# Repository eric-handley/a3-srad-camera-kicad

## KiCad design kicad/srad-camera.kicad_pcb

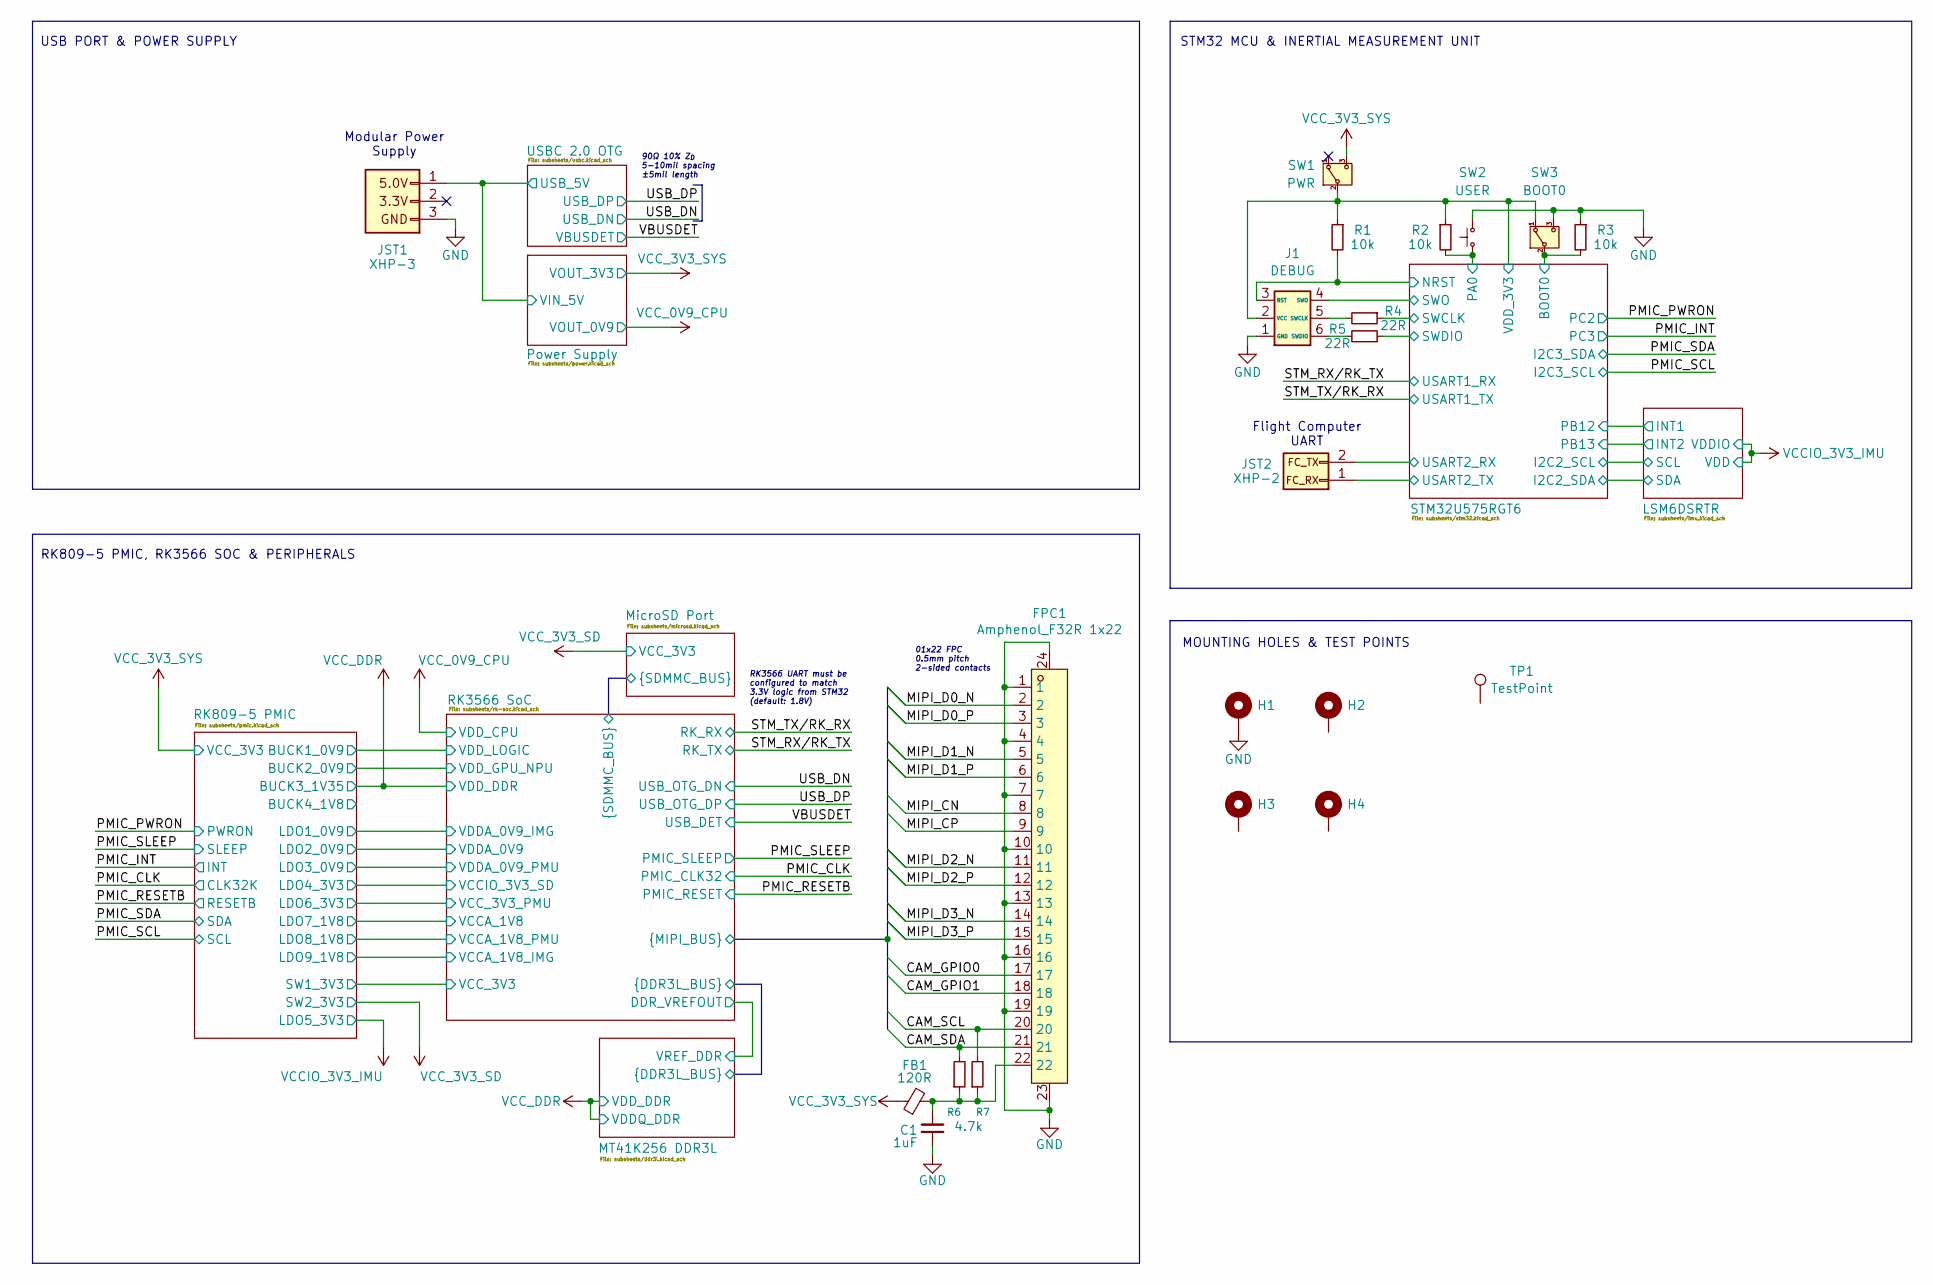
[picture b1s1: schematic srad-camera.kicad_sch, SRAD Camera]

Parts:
C1: 1uF; C_0603_1608Metric; LCSC PART NAME C15849
FB1: 120R; R_0201_0603Metric; LCSC PART NAME C14709
FPC1: Amphenol_F32R 1x22; AMPHENOL_10051922-2210ELF; MANUFACTURER PART 0.5K-AX-22PWB; JLCPCB PART CLASS Extended Part
H1, H2, H3, H4: MntHole; 4-40_MountingHole
J1: DEBUG; PinHeader_2x03_P1.27mm_Vertical
JST1: XHP-3; JST_XH_B3B-XH-A_1x03_P2.50mm_Vertical
JST2: XHP-2; JST_XH_B2B-XH-A_1x02_P2.50mm_Vertical
R1, R2, R3: 10k; R_0402_1005Metric; LCSC PART NAME C25744
R4, R5: 22R; R_0402_1005Metric; LCSC PART NAME C25092
R6, R7: 4.7k; R_0402_1005Metric; LCSC PART NAME C25900
SW1: PWR; SW_SPDT_PCM12
SW2: USER; SW_SPST_EVQP2_MiddlePushTravel_H2.5mm
SW3: BOOT0; SW_SPDT_PCM12
TP1: TestPoint

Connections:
/Power Supply/VIN_5V: JST1.1; also elsewhere on the board
/RK3566 SoC/CAM_GPIO0: FPC1.17; also elsewhere on the board
/RK3566 SoC/CAM_GPIO1: FPC1.18; also elsewhere on the board
/RK3566 SoC/CAM_SCL: FPC1.20, R7.2; also elsewhere on the board
/RK3566 SoC/CAM_SDA: FPC1.21, R6.2; also elsewhere on the board
/RK3566 SoC/MIPI_CN: FPC1.8; also elsewhere on the board
/RK3566 SoC/MIPI_CP: FPC1.9; also elsewhere on the board
/RK3566 SoC/MIPI_D0_N: FPC1.2; also elsewhere on the board
/RK3566 SoC/MIPI_D0_P: FPC1.3; also elsewhere on the board
/RK3566 SoC/MIPI_D1_N: FPC1.5; also elsewhere on the board
/RK3566 SoC/MIPI_D1_P: FPC1.6; also elsewhere on the board
/RK3566 SoC/MIPI_D2_N: FPC1.11; also elsewhere on the board
/RK3566 SoC/MIPI_D2_P: FPC1.12; also elsewhere on the board
/RK3566 SoC/MIPI_D3_N: FPC1.14; also elsewhere on the board
/RK3566 SoC/MIPI_D3_P: FPC1.15; also elsewhere on the board
/STM32U575RGT6/BOOT0: R3.2, SW3.2 (B); also elsewhere on the board
/STM32U575RGT6/NRST: J1.3 (RST), R1.2; also elsewhere on the board
/STM32U575RGT6/PA0: R2.2, SW2.1; also elsewhere on the board
/STM32U575RGT6/SWCLK: R4.1; also elsewhere on the board
/STM32U575RGT6/SWDIO: R5.1; also elsewhere on the board
/STM32U575RGT6/SWO: J1.4 (SWO); also elsewhere on the board
/STM32U575RGT6/USART2_RX: JST2.2; also elsewhere on the board
/STM32U575RGT6/USART2_TX: JST2.1; also elsewhere on the board
/STM32U575RGT6/VDD_3V3: J1.2 (VCC), R1.1, R2.1, SW1.2 (B), SW3.1 (A); also elsewhere on the board
GND: C1.1, FPC1.1, FPC1.4, FPC1.7, FPC1.10, FPC1.13, FPC1.16, FPC1.19, FPC1.23, FPC1.24, H1.1 (MP), J1.1 (GND), JST1.3, R3.1, SW2.2, SW3.3 (C); also elsewhere on the board
unnamed: C1.2, FB1.2, FPC1.22, R6.1, R7.1
unnamed: J1.5 (SWCLK), R4.2
unnamed: J1.6 (SWDIO), R5.2
VCC_3V3_SYS: FB1.1, SW1.3 (C); also elsewhere on the board

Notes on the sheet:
STM32 MCU & INERTIAL MEASUREMENT UNIT
USB PORT & POWER SUPPLY
01x22 FPC 0.5mm pitch 2-sided contacts
90Ω 10% Z_{D} 5-10mil spacing ±5mil length
RK3566 UART must be configured to match 3.3V logic from STM32 (default: 1.8V)
RK809-5 PMIC, RK3566 SOC & PERIPHERALS
Modular Power Supply
Flight Computer UART
MOUNTING HOLES & TEST POINTS

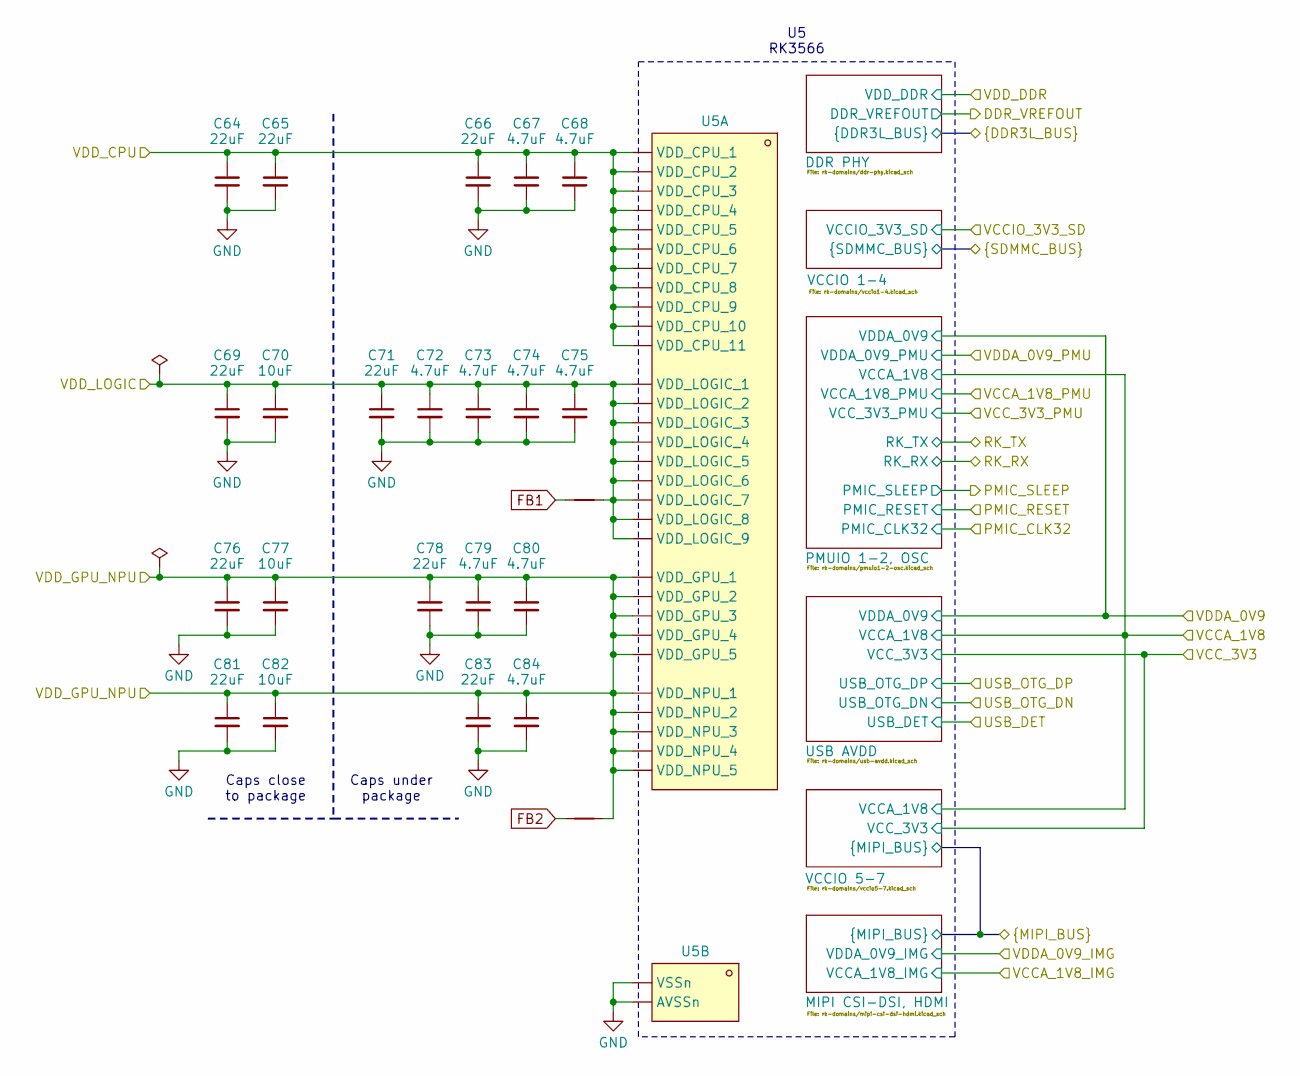
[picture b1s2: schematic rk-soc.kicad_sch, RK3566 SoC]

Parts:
C64, C65, C66, C69, C71, C76, C78, C81, C83: 22uF; C_1206_3216Metric; LCSC PART NAME C12891
C67, C68, C72, C73, C74, C75, C79, C80, C84: 4.7uF; C_0402_1005Metric; LCSC PART NAME C1779
C70, C77, C82: 10uF; C_0805_2012Metric; LCSC PART NAME C15850
NT3, NT4: NetTie_2
U5: RK3566; BGA-565_L15.5-W14.4-P0.40_RK3566_1; MANUFACTURER PART RK3566; JLCPCB PART CLASS Extended Part

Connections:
/RK3566 SoC/VDD_GPU_NPU: C76.1, C77.1, C78.1, C79.1, C80.1, C81.1, C82.1, C83.1, C84.1, NT4.2, U5.1G15 (VDD_NPU_1), U5.1H14 (VDD_NPU_2), U5.1H15 (VDD_NPU_3), U5.1J14 (VDD_NPU_4), U5.1J15 (VDD_NPU_5), U5.1L8 (VDD_GPU_1), U5.1L9 (VDD_GPU_2), U5.1M7 (VDD_GPU_3), U5.1M8 (VDD_GPU_4), U5.1M9 (VDD_GPU_5); also elsewhere on the board
/RK3566 SoC/VDD_LOGIC: C69.1, C70.1, C71.1, C72.1, C73.1, C74.1, C75.1, NT3.2, U5.1H7 (VDD_LOGIC_1), U5.1H8 (VDD_LOGIC_2), U5.1H9 (VDD_LOGIC_3), U5.1H10 (VDD_LOGIC_4), U5.1J7 (VDD_LOGIC_5), U5.1J10 (VDD_LOGIC_6), U5.1K7 (VDD_LOGIC_7), U5.1K10 (VDD_LOGIC_8), U5.1L7 (VDD_LOGIC_9); also elsewhere on the board
GND: C64.2, C65.2, C66.2, C67.2, C68.2, C69.2, C70.2, C71.2, C72.2, C73.2, C74.2, C75.2, C76.2, C77.2, C78.2, C79.2, C80.2, C81.2, C82.2, C83.2, C84.2, U5.1B10 (VSS_30), U5.1B11 (VSS_31), U5.1B15 (VSS_32), U5.1B19 (VSS_33), U5.1C4 (VSS_34), U5.1C5 (VSS_35), U5.1C6 (VSS_36), U5.1C8 (VSS_37), U5.1C9 (VSS_38), U5.1C14 (VSS_39), U5.1C16 (VSS_40), U5.1C18 (VSS_41), U5.1D1 (VSS_42), U5.1D3 (VSS_43), U5.1D10 (VSS_44), U5.1D14 (VSS_45), U5.1E3 (VSS_46), U5.1E8 (VSS_47), U5.1E10 (VSS_48), U5.1E14 (VSS_49), U5.1E15 (VSS_50), U5.1E17 (VSS_51), U5.1F6 (VSS_52), U5.1F7 (VSS_53), U5.1F8 (VSS_54), U5.1F9 (VSS_55), U5.1F10 (VSS_56), U5.1F15 (VSS_57), U5.1F16 (VSS_58), U5.1F20 (AVSS1_6), U5.1G3 (VSS_59), U5.1G6 (VSS_60), U5.1G7 (VSS_61), U5.1G8 (VSS_62), U5.1G9 (VSS_63), U5.1G10 (VSS_64), U5.1G11 (VSS_65), U5.1G12 (VSS_66), U5.1G14 (VSS_67), U5.1G16 (AVSS1_7), U5.1G18 (AVSS1_8), U5.1G19 (AVSS1_9), U5.1G20 (AVSS1_10), U5.1H1 (VSS_68), U5.1H2 (VSS_69), U5.1H6 (VSS_70), U5.1H11 (VSS_71), U5.1H12 (VSS_72), U5.1H13 (VSS_73), U5.1J1 (VSS_74), U5.1J6 (VSS_75), U5.1J8 (VSS_76), U5.1J9 (VSS_77), U5.1J11 (VSS_78), U5.1J12 (VSS_79), U5.1J13 (VSS_80), U5.1J16 (AVSS1_11), U5.1J18 (AVSS1_12), U5.1K2 (VSS_81), U5.1K3 (VSS_82), U5.1K4 (VSS_83), U5.1K5 (VSS_84), U5.1K6 (VSS_85), U5.1K8 (VSS_86), U5.1K9 (VSS_87), U5.1K11 (VSS_88), U5.1K12 (VSS_89), U5.1K13 (VSS_90), U5.1K14 (VSS_91), U5.1K15 (VSS_92), U5.1K18 (AVSS1_13), U5.1L3 (VSS_93), U5.1L6 (VSS_94), U5.1L10 (VSS_95), U5.1L11 (VSS_96), U5.1L12 (VSS_97), U5.1L13 (VSS_98), U5.1L14 (VSS_99), U5.1L15 (VSS_100), U5.1L19 (AVSS1_14), U5.1M3 (VSS_101), U5.1M4 (VSS_102), U5.1M5 (VSS_103), U5.1M6 (VSS_104), U5.1M10 (VSS_105), U5.1M11 (VSS_106), U5.1M12 (VSS_107), U5.1M13 (VSS_108), U5.1M14 (VSS_109), U5.1M15 (VSS_110), U5.1M16 (VSS_111), U5.1M17 (VSS_112), U5.1M20 (VSS_113), U5.1N3 (VSS_114), U5.1N4 (VSS_115), U5.1N7 (VSS_116), U5.1N11 (AVSS_9), U5.1N12 (AVSS_10), U5.1P1 (VSS_117), U5.1P5 (VSS_118), U5.1P6 (VSS_119), U5.1P7 (VSS_120), U5.1P8 (AVSS_11), U5.1P10 (AVSS_12), U5.1P14 (AVSS_13), U5.1P15 (VSS_121), U5.1R3 (VSS_122), U5.1R4 (VSS_123), U5.1R5 (VSS_124), U5.1R6 (VSS_125), U5.1R7 (VSS_126), U5.1R8 (AVSS_14), U5.1R9 (AVSS_15), U5.1R11 (AVSS_16), U5.1R12 (AVSS_17), U5.1R13 (AVSS_18), U5.1R14 (AVSS_19), U5.1R15 (AVSS_20), U5.1T3 (VSS_127), U5.1T5 (VSS_128), U5.1T7 (AVSS_21), U5.1T8 (AVSS_22), U5.1T9 (AVSS_23), U5.1T10 (AVSS_24), U5.1T11 (AVSS_25), U5.1T12 (AVSS_26), U5.1T13 (AVSS_27), U5.1T14 (AVSS_28), U5.1T15 (AVSS_29), U5.1T16 (AVSS_30), U5.1T17 (AVSS_31), U5.1U2 (VSS_129), U5.1U12 (AVSS_32), U5.1U13 (AVSS_33), U5.1U15 (AVSS_34), U5.1U17 (AVSS_35), U5.1V1 (VSS_130), U5.1V4 (VSS_131), U5.1V7 (AVSS_36), U5.1V12 (AVSS_37), U5.1V13 (AVSS_38), U5.1V18 (AVSS_39), U5.A1 (VSSn), U5.A2 (VSS_2), U5.A38 (VSS_3), U5.AA2 (VSS_18), U5.AC37 (VSS_24), U5.AD2 (VSS_19), U5.AE37 (VSS_25), U5.AH37 (VSS_26), U5.AL37 (VSS_27), U5.AP2 (VSS_20), U5.AP8 (VSS_22), U5.AP13 (AVSS_1), U5.AP16 (AVSS_2), U5.AP19 (AVSS_3), U5.AP22 (AVSS_4), U5.AP25 (AVSS_5), U5.AP28 (AVSS_6), U5.AP31 (AVSS_7), U5.AP34 (AVSS_8), U5.AP37 (VSS_28), U5.AR1 (VSS_21), U5.AR38 (VSS_29), U5.B1 (VSS_4), U5.B2 (VSS_5), U5.B6 (VSS_6), U5.B11 (VSS_7), U5.B14 (VSS_8), U5.B18 (VSS_9), U5.B21 (VSS_10), U5.B28 (VSS_11), U5.B31 (VSS_12), U5.D2 (VSS_13), U5.E37 (VSS_23), U5.H37 (AVSSn), U5.J2 (VSS_14), U5.L2 (VSS_15), U5.L37 (AVSS1_2), U5.P37 (AVSS1_3), U5.U2 (VSS_16), U5.U37 (AVSS1_4), U5.W2 (VSS_17), U5.Y37 (AVSS1_5); also elsewhere on the board
VCC_0V9_CPU: C64.1, C65.1, C66.1, C67.1, C68.1, U5.1C12 (VDD_CPU_1), U5.1D11 (VDD_CPU_2), U5.1D12 (VDD_CPU_3), U5.1E11 (VDD_CPU_4), U5.1E12 (VDD_CPU_5), U5.1E13 (VDD_CPU_6), U5.1F11 (VDD_CPU_7), U5.1F12 (VDD_CPU_8), U5.1F13 (VDD_CPU_9), U5.1F14 (VDD_CPU_10), U5.1G13 (VDD_CPU_11); also elsewhere on the board

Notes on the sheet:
U5 RK3566
Caps close to package
Caps under package

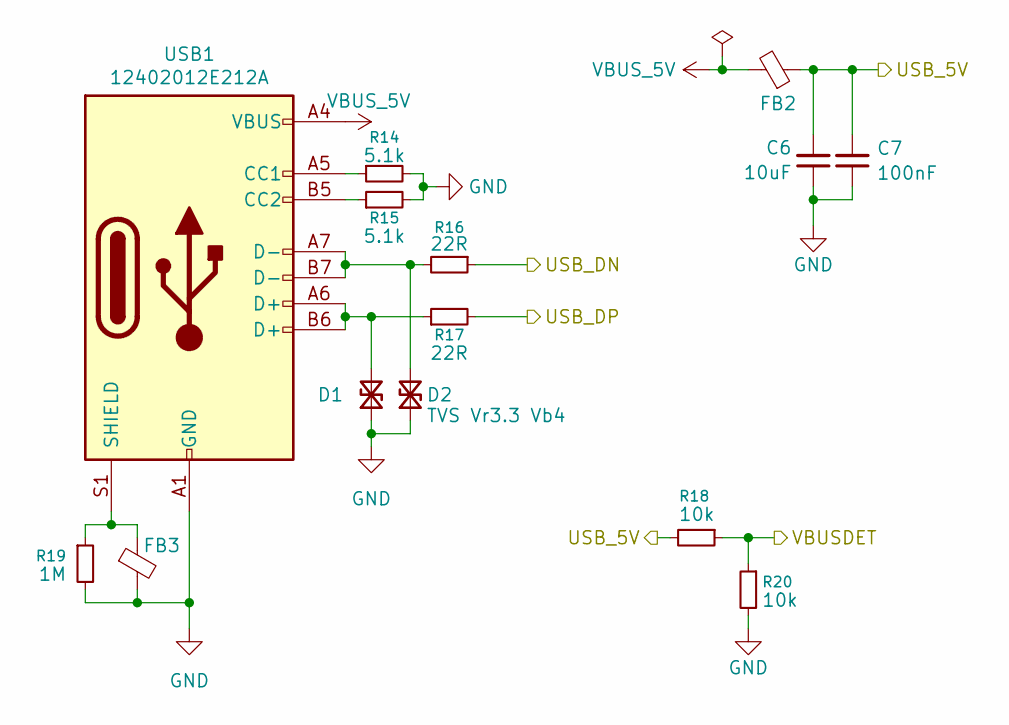
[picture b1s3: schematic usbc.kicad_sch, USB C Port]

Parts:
C6: 10uF; C_0805_2012Metric; LCSC PART NAME C15850
C7: 100nF; C_0402_1005Metric; LCSC PART NAME C1525
D1, D2: TVS Vr3.3 Vb4; D_SOD-123F; LCSC PART NAME C19077496
FB2, FB3: 120R; R_0201_0603Metric; LCSC PART NAME C14709
R14, R15: 5.1k; R_0402_1005Metric; LCSC PART NAME C25905
R16, R17: 22R; R_0402_1005Metric; LCSC PART NAME C25092
R18, R20: 10k; R_0402_1005Metric; LCSC PART NAME C25744
R19: 1M; R_0402_1005Metric; LCSC PART NAME C26083
USB1: 12402012E212A; USB_C_Receptacle_HRO_TYPE-C-31-M-12

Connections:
/Power Supply/VIN_5V: C6.2, C7.2, FB2.1, R18.2; also elsewhere on the board
/USB_DN: R16.1; also elsewhere on the board
/USB_DP: R17.2; also elsewhere on the board
/VBUSDET: R18.1, R20.1; also elsewhere on the board
GND: C6.1, C7.1, D1.1 (A1), D2.1 (A1), FB3.2, R14.2, R15.2, R19.2, R20.2, USB1.A1 (GND), USB1.A12 (GND), USB1.B1 (GND), USB1.B12 (GND); also elsewhere on the board
unnamed: D1.2 (A2), R17.1, USB1.A6 (D+), USB1.B6 (D+)
unnamed: D2.2 (A2), R16.2, USB1.A7 (D-), USB1.B7 (D-)
unnamed: R14.1, USB1.A5 (CC1)
unnamed: R15.1, USB1.B5 (CC2)
unnamed: FB3.1, R19.1, USB1.S1 (SHIELD)
VBUS_5V: FB2.2, USB1.A4 (VBUS), USB1.A9 (VBUS), USB1.B4 (VBUS), USB1.B9 (VBUS)

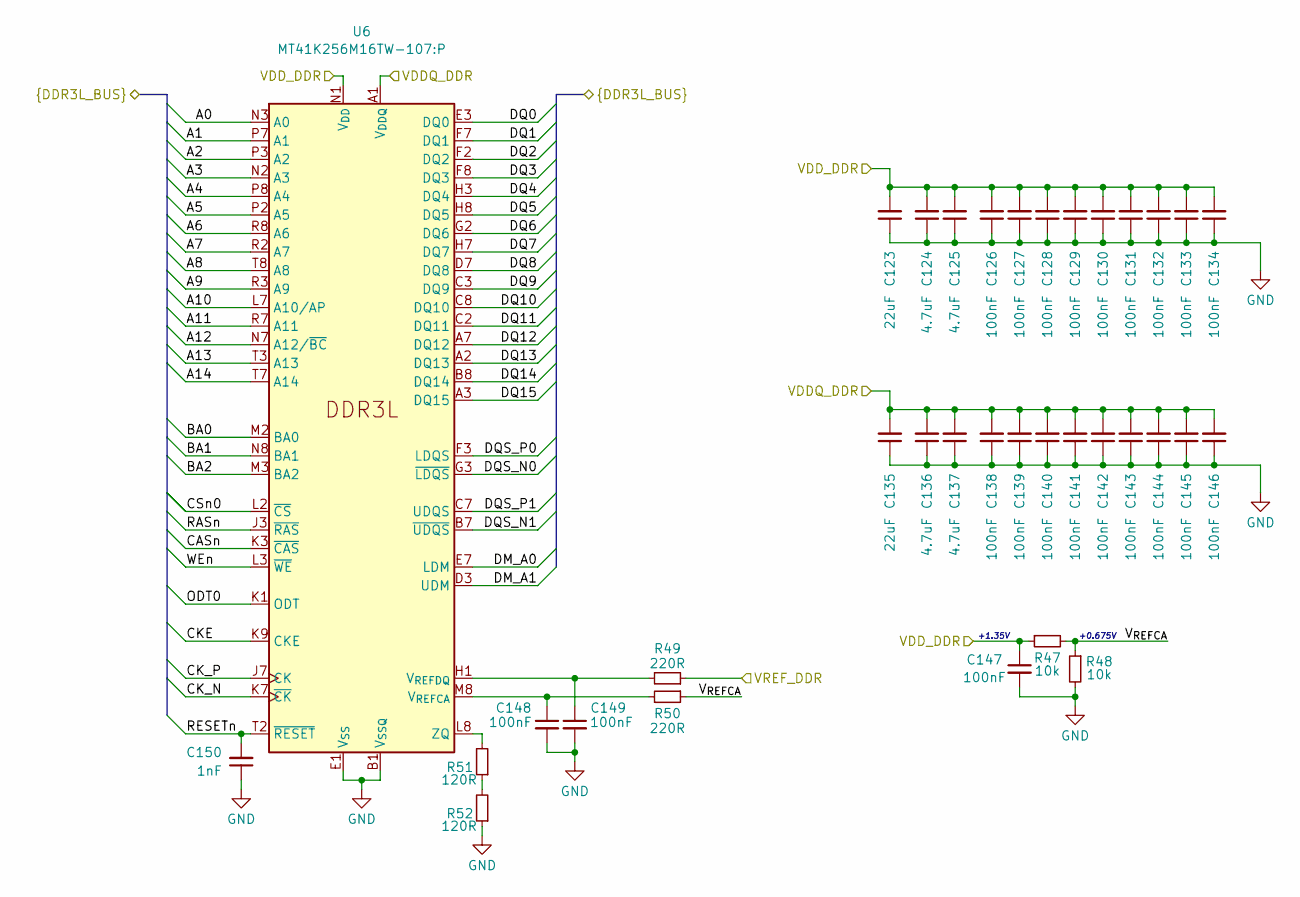
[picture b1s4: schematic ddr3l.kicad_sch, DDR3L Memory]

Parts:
C123, C135: 22uF; C_1206_3216Metric; LCSC PART NAME C12891
C124, C125, C136, C137: 4.7uF; C_0805_2012Metric; LCSC PART NAME C1779
C126, C127, C128, C129, C130, C131, C132, C133, C134, C138, C139, C140, C141, C142, C143, C144, C145, C146, C147, C148, C149: 100nF; C_0402_1005Metric; LCSC PART NAME C1525
C150: 1nF; C_0402_1005Metric; LCSC PART NAME C1523
R47, R48: 10k; R_0603_1608Metric; LCSC PART NAME C25804
R49, R50: 220R; R_0603_1608Metric; LCSC PART NAME C22962
R51, R52: 120R; R_0402_1005Metric; LCSC PART NAME C25079
U6: MT41K256M16TW-107:P; Micron_FBGA-96_8x14mm_Layout9x16_P0.8mm

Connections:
/MT41K256 DDR3L/A0: U6.N3 (A0); also elsewhere on the board
/MT41K256 DDR3L/A1: U6.P7 (A1); also elsewhere on the board
/MT41K256 DDR3L/A2: U6.P3 (A2); also elsewhere on the board
/MT41K256 DDR3L/A3: U6.N2 (A3); also elsewhere on the board
/MT41K256 DDR3L/A4: U6.P8 (A4); also elsewhere on the board
/MT41K256 DDR3L/A5: U6.P2 (A5); also elsewhere on the board
/MT41K256 DDR3L/A6: U6.R8 (A6); also elsewhere on the board
/MT41K256 DDR3L/A7: U6.R2 (A7); also elsewhere on the board
/MT41K256 DDR3L/A8: U6.T8 (A8); also elsewhere on the board
/MT41K256 DDR3L/A9: U6.R3 (A9); also elsewhere on the board
/MT41K256 DDR3L/A10: U6.L7 (A10/AP); also elsewhere on the board
/MT41K256 DDR3L/A11: U6.R7 (A11); also elsewhere on the board
/MT41K256 DDR3L/A12: U6.N7 (A12/~BC); also elsewhere on the board
/MT41K256 DDR3L/A13: U6.T3 (A13); also elsewhere on the board
/MT41K256 DDR3L/A14: U6.T7 (A14); also elsewhere on the board
/MT41K256 DDR3L/BA0: U6.M2 (BA0); also elsewhere on the board
/MT41K256 DDR3L/BA1: U6.N8 (BA1); also elsewhere on the board
/MT41K256 DDR3L/BA2: U6.M3 (BA2); also elsewhere on the board
/MT41K256 DDR3L/CASn: U6.K3 (~CAS); also elsewhere on the board
/MT41K256 DDR3L/CKE: U6.K9 (CKE); also elsewhere on the board
/MT41K256 DDR3L/CK_N: U6.K7 (~CK); also elsewhere on the board
/MT41K256 DDR3L/CK_P: U6.J7 (CK); also elsewhere on the board
/MT41K256 DDR3L/CSn0: U6.L2 (~CS); also elsewhere on the board
/MT41K256 DDR3L/DM_A0: U6.E7 (LDM); also elsewhere on the board
/MT41K256 DDR3L/DM_A1: U6.D3 (UDM); also elsewhere on the board
/MT41K256 DDR3L/DQ0: U6.E3 (DQ0); also elsewhere on the board
/MT41K256 DDR3L/DQ1: U6.F7 (DQ1); also elsewhere on the board
/MT41K256 DDR3L/DQ2: U6.F2 (DQ2); also elsewhere on the board
/MT41K256 DDR3L/DQ3: U6.F8 (DQ3); also elsewhere on the board
/MT41K256 DDR3L/DQ4: U6.H3 (DQ4); also elsewhere on the board
/MT41K256 DDR3L/DQ5: U6.H8 (DQ5); also elsewhere on the board
/MT41K256 DDR3L/DQ6: U6.G2 (DQ6); also elsewhere on the board
/MT41K256 DDR3L/DQ7: U6.H7 (DQ7); also elsewhere on the board
/MT41K256 DDR3L/DQ8: U6.D7 (DQ8); also elsewhere on the board
/MT41K256 DDR3L/DQ9: U6.C3 (DQ9); also elsewhere on the board
/MT41K256 DDR3L/DQ10: U6.C8 (DQ10); also elsewhere on the board
/MT41K256 DDR3L/DQ11: U6.C2 (DQ11); also elsewhere on the board
/MT41K256 DDR3L/DQ12: U6.A7 (DQ12); also elsewhere on the board
/MT41K256 DDR3L/DQ13: U6.A2 (DQ13); also elsewhere on the board
/MT41K256 DDR3L/DQ14: U6.B8 (DQ14); also elsewhere on the board
/MT41K256 DDR3L/DQ15: U6.A3 (DQ15); also elsewhere on the board
/MT41K256 DDR3L/DQS_N0: U6.G3 (~LDQS); also elsewhere on the board
/MT41K256 DDR3L/DQS_N1: U6.B7 (~UDQS); also elsewhere on the board
/MT41K256 DDR3L/DQS_P0: U6.F3 (LDQS); also elsewhere on the board
/MT41K256 DDR3L/DQS_P1: U6.C7 (UDQS); also elsewhere on the board
/MT41K256 DDR3L/ODT0: U6.K1 (ODT); also elsewhere on the board
/MT41K256 DDR3L/RASn: U6.J3 (~RAS); also elsewhere on the board
/MT41K256 DDR3L/RESETn: C150.2, U6.T2 (~RESET); also elsewhere on the board
/MT41K256 DDR3L/VREF_DDR: R49.1; also elsewhere on the board
/MT41K256 DDR3L/V_{REFCA}: R47.2, R48.1, R50.1
/MT41K256 DDR3L/WEn: U6.L3 (~WE); also elsewhere on the board
GND: C123.1, C124.1, C125.1, C126.1, C127.1, C128.1, C129.1, C130.1, C131.1, C132.1, C133.1, C134.1, C135.1, C136.1, C137.1, C138.1, C139.1, C140.1, C141.1, C142.1, C143.1, C144.1, C145.1, C146.1, C147.2, C148.2, C149.2, C150.1, R48.2, R52.1, U6.A9 (V_{SS}), U6.B1 (V_{SSQ}), U6.B3 (V_{SS}), U6.B9 (V_{SSQ}), U6.D1 (V_{SSQ}), U6.D8 (V_{SSQ}), U6.E1 (V_{SS}), U6.E2 (V_{SSQ}), U6.E8 (V_{SSQ}), U6.F9 (V_{SSQ}), U6.G1 (V_{SSQ}), U6.G8 (V_{SS}), U6.G9 (V_{SSQ}), U6.J2 (V_{SS}), U6.J8 (V_{SS}), U6.M1 (V_{SS}), U6.M9 (V_{SS}), U6.P1 (V_{SS}), U6.P9 (V_{SS}), U6.T1 (V_{SS}), U6.T9 (V_{SS}); also elsewhere on the board
unnamed: R51.1, R52.2
unnamed: C148.1, R50.2, U6.M8 (V_{REFCA})
unnamed: C149.1, R49.2, U6.H1 (V_{REFDQ})
unnamed: R51.2, U6.L8 (ZQ)
VCC_DDR: C123.2, C124.2, C125.2, C126.2, C127.2, C128.2, C129.2, C130.2, C131.2, C132.2, C133.2, C134.2, C135.2, C136.2, C137.2, C138.2, C139.2, C140.2, C141.2, C142.2, C143.2, C144.2, C145.2, C146.2, C147.1, R47.1, U6.A1 (V_{DDQ}), U6.A8 (V_{DDQ}), U6.B2 (V_{DD}), U6.C1 (V_{DDQ}), U6.C9 (V_{DDQ}), U6.D2 (V_{DDQ}), U6.D9 (V_{DD}), U6.E9 (V_{DDQ}), U6.F1 (V_{DDQ}), U6.G7 (V_{DD}), U6.H2 (V_{DDQ}), U6.H9 (V_{DDQ}), U6.K2 (V_{DD}), U6.K8 (V_{DD}), U6.N1 (V_{DD}), U6.N9 (V_{DD}), U6.R1 (V_{DD}), U6.R9 (V_{DD}); also elsewhere on the board

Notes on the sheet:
+1.35V
+0.675V

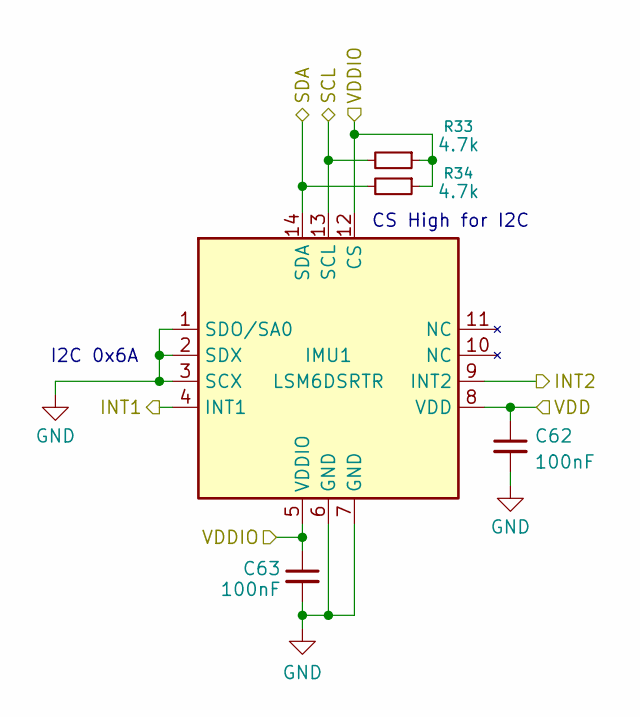
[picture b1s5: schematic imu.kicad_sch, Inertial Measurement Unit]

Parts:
C62, C63: 100nF; C_0402_1005Metric; LCSC PART NAME C1525
IMU1: LSM6DSRTR; LGA-14_3x2.5mm_P0.5mm_LayoutBorder3x4y
R33, R34: 4.7k; R_0402_1005Metric; LCSC PART NAME C25900

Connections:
/LSM6DSRTR/INT1: IMU1.4 (INT1); also elsewhere on the board
/LSM6DSRTR/INT2: IMU1.9 (INT2); also elsewhere on the board
/LSM6DSRTR/SCL: IMU1.13 (SCL), R33.2; also elsewhere on the board
/LSM6DSRTR/SDA: IMU1.14 (SDA), R34.2; also elsewhere on the board
GND: C62.2, C63.2, IMU1.1 (SDO/SA0), IMU1.2 (SDX), IMU1.3 (SCX), IMU1.6 (GND), IMU1.7 (GND); also elsewhere on the board
VCCIO_3V3_IMU: C62.1, C63.1, IMU1.5 (VDDIO), IMU1.8 (VDD), IMU1.12 (CS), R33.1, R34.1; also elsewhere on the board

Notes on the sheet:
CS High for I2C
I2C 0x6A

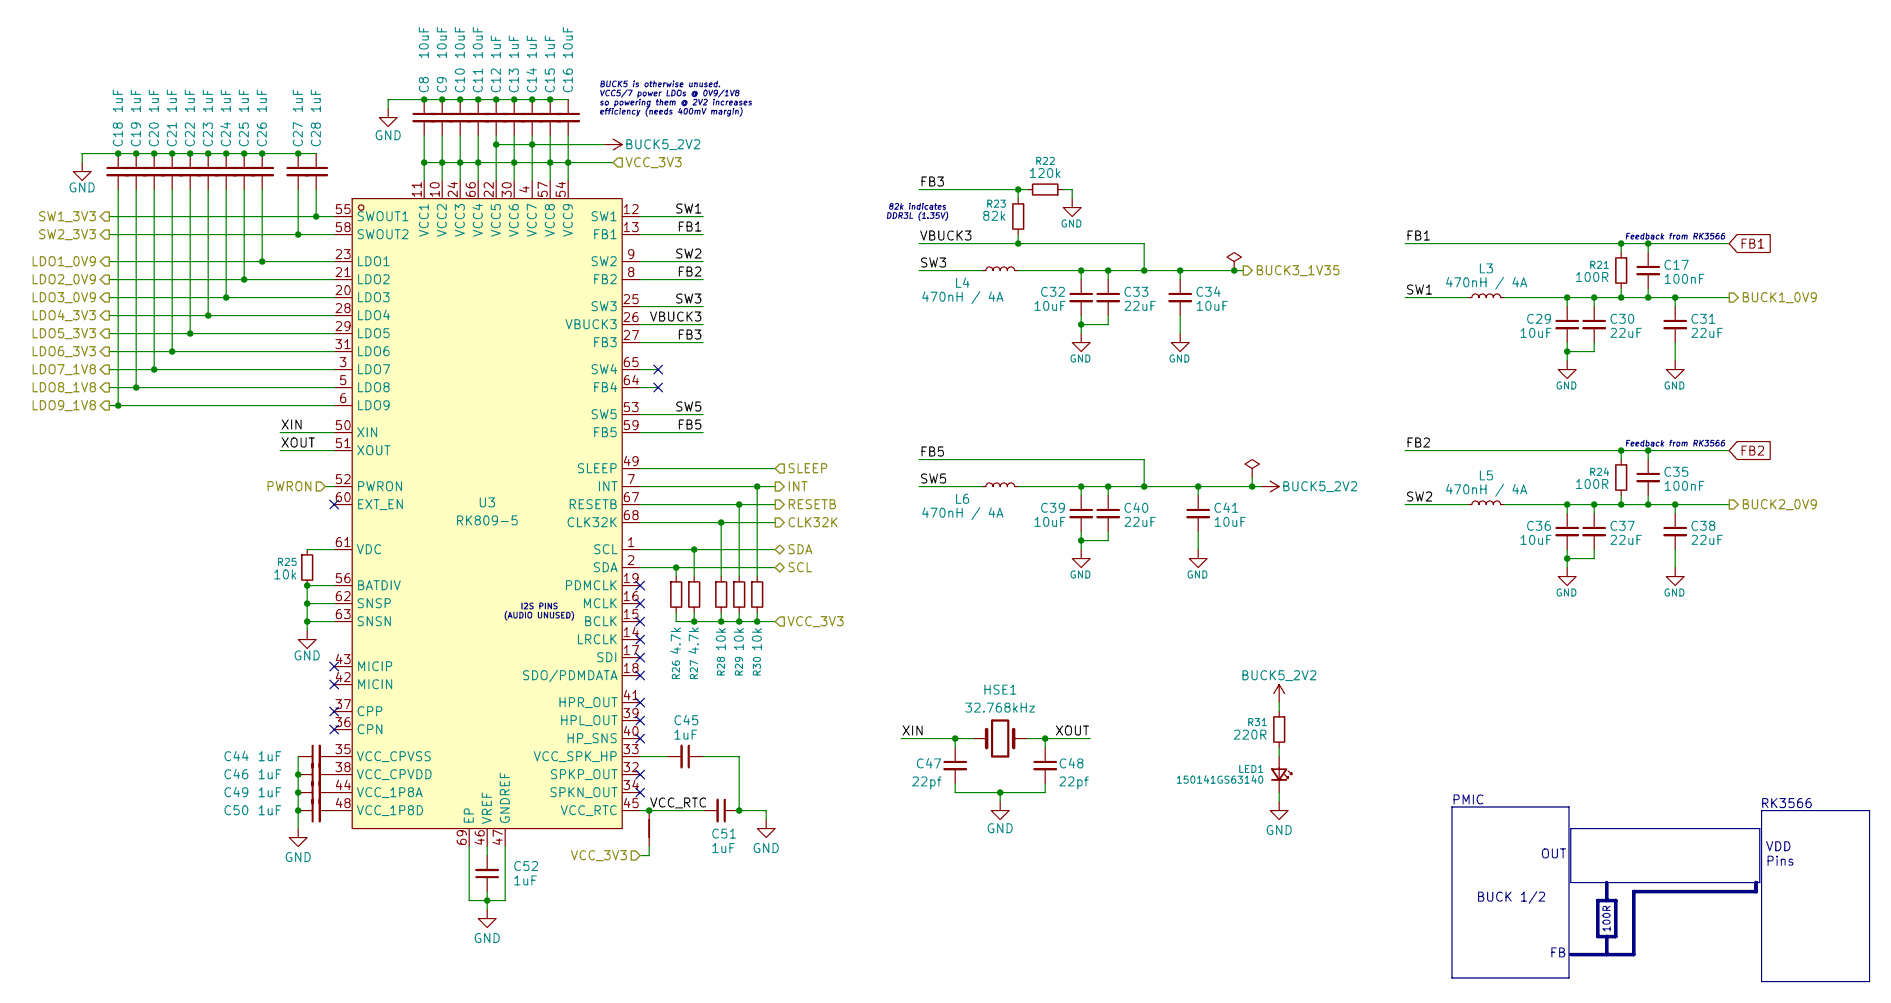
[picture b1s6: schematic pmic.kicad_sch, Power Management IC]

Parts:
C8, C9, C10, C11, C16, C29, C32, C34, C36, C39, C41: 10uF; C_0805_2012Metric; LCSC PART NAME C15850
C12, C13, C14, C15, C18, C19, C20, C21, C22, C23, C24, C25, C26, C27, C28, C44, C45, C46, C49, C50, C51, C52: 1uF; C_0603_1608Metric; LCSC PART NAME C15849
C17, C35: 100nF; C_0402_1005Metric; LCSC PART NAME C1525
C30, C31, C33, C37, C38, C40: 22uF; C_1206_3216Metric; LCSC PART NAME C12891
C47, C48: 22pf; C_0402_1005Metric; LCSC PART NAME C1555
HSE1: 32.768kHz; Crystal_SMD_3215-2Pin_3.2x1.5mm; LCSC PART NAME C32346
L3, L4, L5, L6: 470nH / 4A; L_0805_2012Metric; LCSC PART NAME C89446
LED1: 150141GS63140; LED_0805_2012Metric; LCSC PART NAME C2297
NT2: NetTie_2
R21, R24: 100R; R_0402_1005Metric; LCSC PART NAME C25076
R22: 120k; R_0603_1608Metric; LCSC PART NAME C25808
R23: 82k; R_0603_1608Metric; LCSC PART NAME C23254
R25, R28, R29, R30: 10k; R_0402_1005Metric; LCSC PART NAME C25744
R26, R27: 4.7k; R_0402_1005Metric; LCSC PART NAME C25900
R31: 220R; R_0603_1608Metric; LCSC PART NAME C22962
U3: RK809-5; ArtInChip_QFN-68-1EP_7x7mm_P0.35mm_EP5.49x5.49mm; MANUFACTURER PART RK809-5; JLCPCB PART CLASS Extended Part

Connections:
/PMIC_CLK: R28.1, U3.68 (CLK32K); also elsewhere on the board
/PMIC_INT: R30.1, U3.7 (INT); also elsewhere on the board
/PMIC_PWRON: U3.52 (PWRON); also elsewhere on the board
/PMIC_RESETB: R29.1, U3.67 (RESETB); also elsewhere on the board
/PMIC_SCL: R26.1, U3.2 (SDA); also elsewhere on the board
/PMIC_SDA: R27.1, U3.1 (SCL); also elsewhere on the board
/PMIC_SLEEP: U3.49 (SLEEP); also elsewhere on the board
/RK809-5 PMIC/FB3: R22.2, R23.1, U3.27 (FB3)
/RK809-5 PMIC/SW1: L3.1, U3.12 (SW1)
/RK809-5 PMIC/SW2: L5.1, U3.9 (SW2)
/RK809-5 PMIC/SW3: L4.1, U3.25 (SW3)
/RK809-5 PMIC/SW5: L6.1, U3.53 (SW5)
/RK809-5 PMIC/VCC_RTC: C51.2, NT2.2, U3.45 (VCC_RTC)
/RK809-5 PMIC/XIN: C47.1, HSE1.1, U3.50 (XIN)
/RK809-5 PMIC/XOUT: C48.1, HSE1.2, U3.51 (XOUT)
/RK3566 SoC/VCCA_1V8: C20.2, U3.3 (LDO7); also elsewhere on the board
/RK3566 SoC/VCCA_1V8_IMG: C18.2, U3.6 (LDO9); also elsewhere on the board
/RK3566 SoC/VCCA_1V8_PMU: C19.2, U3.5 (LDO8); also elsewhere on the board
/RK3566 SoC/VCCIO_3V3_SD: C23.2, U3.28 (LDO4); also elsewhere on the board
/RK3566 SoC/VCC_3V3: C28.2, U3.55 (SWOUT1); also elsewhere on the board
/RK3566 SoC/VCC_3V3_PMU: C21.2, U3.31 (LDO6); also elsewhere on the board
/RK3566 SoC/VDDA_0V9: C25.2, U3.21 (LDO2); also elsewhere on the board
/RK3566 SoC/VDDA_0V9_IMG: C26.2, U3.23 (LDO1); also elsewhere on the board
/RK3566 SoC/VDDA_0V9_PMU: C24.2, U3.20 (LDO3); also elsewhere on the board
/RK3566 SoC/VDD_GPU_NPU: C35.2, C36.1, C37.1, C38.1, L5.2, R24.2; also elsewhere on the board
/RK3566 SoC/VDD_LOGIC: C17.2, C29.1, C30.1, C31.1, L3.2, R21.2; also elsewhere on the board
BUCK5_2V2: C12.2, C14.2, C39.1, C40.1, C41.1, L6.2, R31.1, U3.4 (VCC7), U3.22 (VCC5), U3.59 (FB5)
FB1: C17.1, R21.1, U3.13 (FB1)
FB2: C35.1, R24.1, U3.8 (FB2)
GND: C8.1, C9.1, C10.1, C11.1, C12.1, C13.1, C14.1, C15.1, C16.1, C18.1, C19.1, C20.1, C21.1, C22.1, C23.1, C24.1, C25.1, C26.1, C27.1, C28.1, C29.2, C30.2, C31.2, C32.2, C33.2, C34.2, C36.2, C37.2, C38.2, C39.2, C40.2, C41.2, C44.1, C45.1, C46.1, C47.2, C48.2, C49.1, C50.1, C51.1, C52.1, LED1.1 (K), R22.1, R25.2, U3.47 (GNDREF), U3.56 (BATDIV), U3.62 (SNSP), U3.63 (SNSN), U3.69 (EP); also elsewhere on the board
unnamed: LED1.2 (A), R31.2
unnamed: C49.2, U3.44 (VCC_1P8A)
unnamed: C50.2, U3.48 (VCC_1P8D)
unnamed: C46.2, U3.38 (VCC_CPVDD)
unnamed: C44.2, U3.35 (VCC_CPVSS)
unnamed: C45.2, U3.33 (VCC_SPK_HP)
unnamed: R25.1, U3.61 (VDC)
unnamed: C52.2, U3.46 (VREF)
VCCIO_3V3_IMU: C22.2, U3.29 (LDO5); also elsewhere on the board
VCC_3V3_SD: C27.2, U3.58 (SWOUT2); also elsewhere on the board
VCC_3V3_SYS: C8.2, C9.2, C10.2, C11.2, C13.2, C15.2, C16.2, NT2.1, R26.2, R27.2, R28.2, R29.2, R30.2, U3.10 (VCC2), U3.11 (VCC1), U3.24 (VCC3), U3.30 (VCC6), U3.54 (VCC9), U3.57 (VCC8), U3.66 (VCC4); also elsewhere on the board
VCC_DDR: C32.1, C33.1, C34.1, L4.2, R23.2, U3.26 (VBUCK3); also elsewhere on the board

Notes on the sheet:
OUT
100R
PMIC
I2S PINS (AUDIO UNUSED)
82k indicates DDR3L (1.35V)
BUCK5 is otherwise unused. VCC5/7 power LDOs @ 0V9/1V8 so powering them @ 2V2 increases efficiency (needs 400mV margin)
Feedback from RK3566
RK3566
VDD Pins
BUCK 1/2

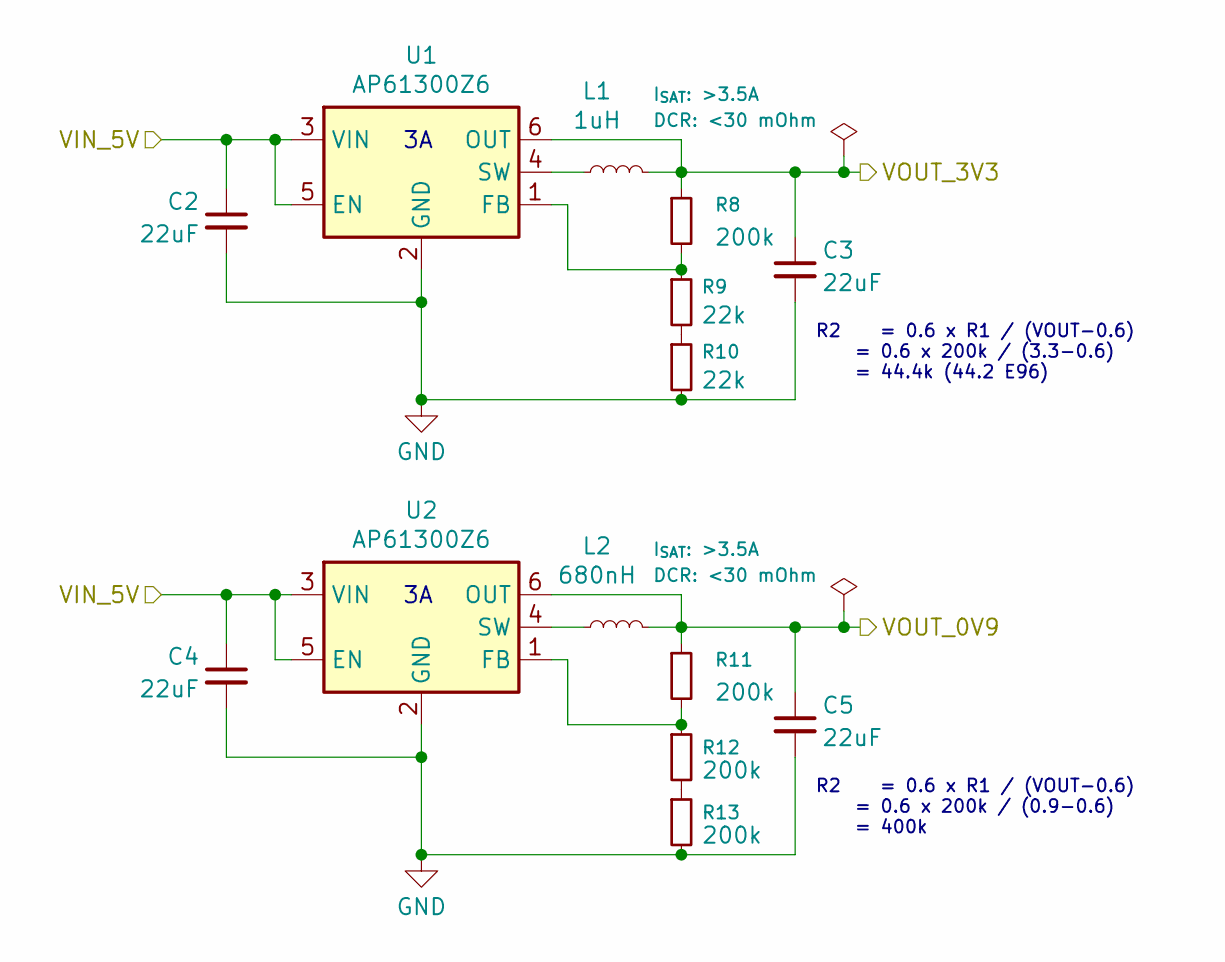
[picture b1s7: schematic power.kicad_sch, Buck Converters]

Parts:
C2, C3, C4, C5: 22uF; C_1206_3216Metric; LCSC PART NAME C12891
L1: 1uH; L_0805_2012Metric; LCSC PART NAME C1042
L2: 680nH; L_0603_1608Metric; LCSC PART NAME C55546
R8, R11, R12, R13: 200k; R_0402_1005Metric; LCSC PART NAME C25764
R9, R10: 22k; R_0402_1005Metric; LCSC PART NAME C25768
U1, U2: AP61300Z6; SOT-563

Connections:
/Power Supply/VIN_5V: C2.1, C4.1, U1.3 (VIN), U1.5 (EN), U2.3 (VIN), U2.5 (EN); also elsewhere on the board
GND: C2.2, C3.2, C4.2, C5.2, R10.2, R13.2, U1.2 (GND), U2.2 (GND); also elsewhere on the board
unnamed: R9.2, R10.1
unnamed: R12.2, R13.1
unnamed: R8.2, R9.1, U1.1 (FB)
unnamed: L1.1, U1.4 (SW)
unnamed: R11.2, R12.1, U2.1 (FB)
unnamed: L2.1, U2.4 (SW)
VCC_0V9_CPU: C5.1, L2.2, R11.1, U2.6 (OUT); also elsewhere on the board
VCC_3V3_SYS: C3.1, L1.2, R8.1, U1.6 (OUT); also elsewhere on the board

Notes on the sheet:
R2 = 0.6 x R1 / (VOUT-0.6) = 0.6 x 200k / (0.9-0.6) = 400k
R2 = 0.6 x R1 / (VOUT-0.6) = 0.6 x 200k / (3.3-0.6) = 44.4k (44.2 E96)

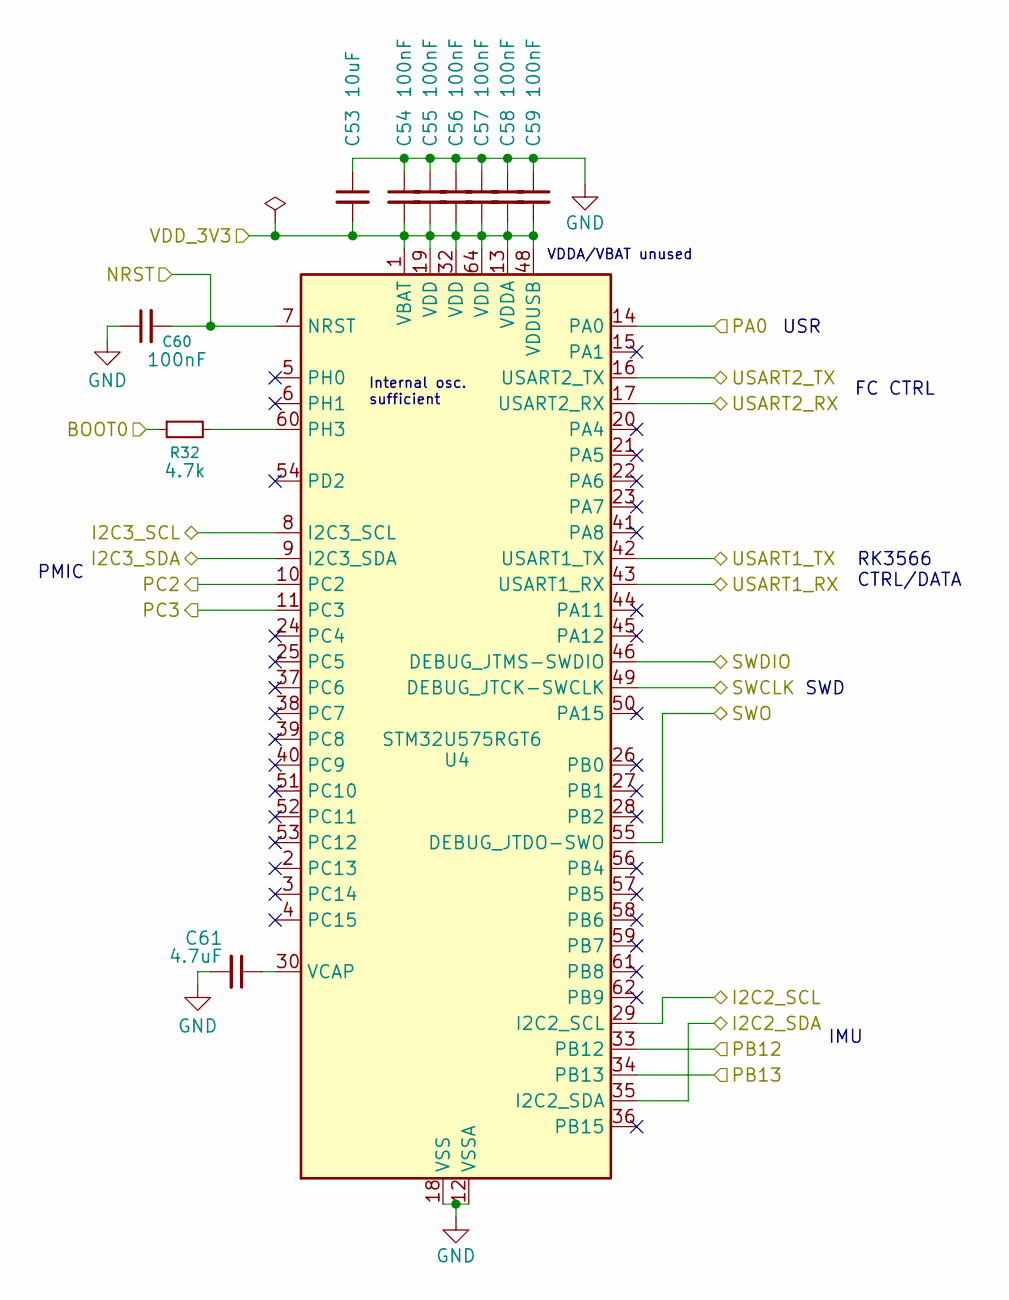
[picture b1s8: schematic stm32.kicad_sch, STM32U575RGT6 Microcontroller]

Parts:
C53: 10uF; C_0805_2012Metric; LCSC PART NAME C15850
C54, C55, C56, C57, C58, C59, C60: 100nF; C_0402_1005Metric; LCSC PART NAME C1525
C61: 4.7uF; C_0805_2012Metric; LCSC PART NAME C1779
R32: 4.7k; R_0402_1005Metric; LCSC PART NAME C25900
U4: STM32U575RGT6; LQFP-64_10x10mm_P0.5mm

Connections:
/LSM6DSRTR/INT1: U4.33 (PB12); also elsewhere on the board
/LSM6DSRTR/INT2: U4.34 (PB13); also elsewhere on the board
/LSM6DSRTR/SCL: U4.29 (I2C2_SCL); also elsewhere on the board
/LSM6DSRTR/SDA: U4.35 (I2C2_SDA); also elsewhere on the board
/PMIC_INT: U4.11 (PC3); also elsewhere on the board
/PMIC_PWRON: U4.10 (PC2); also elsewhere on the board
/PMIC_SCL: U4.8 (I2C3_SCL); also elsewhere on the board
/PMIC_SDA: U4.9 (I2C3_SDA); also elsewhere on the board
/STM32U575RGT6/BOOT0: R32.1; also elsewhere on the board
/STM32U575RGT6/NRST: C60.2, U4.7 (NRST); also elsewhere on the board
/STM32U575RGT6/PA0: U4.14 (PA0); also elsewhere on the board
/STM32U575RGT6/SWCLK: U4.49 (DEBUG_JTCK-SWCLK); also elsewhere on the board
/STM32U575RGT6/SWDIO: U4.46 (DEBUG_JTMS-SWDIO); also elsewhere on the board
/STM32U575RGT6/SWO: U4.55 (DEBUG_JTDO-SWO); also elsewhere on the board
/STM32U575RGT6/USART2_RX: U4.17 (USART2_RX); also elsewhere on the board
/STM32U575RGT6/USART2_TX: U4.16 (USART2_TX); also elsewhere on the board
/STM32U575RGT6/VDD_3V3: C53.2, C54.2, C55.2, C56.2, C57.2, C58.2, C59.2, U4.1 (VBAT), U4.13 (VDDA), U4.19 (VDD), U4.32 (VDD), U4.48 (VDDUSB), U4.64 (VDD); also elsewhere on the board
/STM_RX/RK_TX: U4.43 (USART1_RX); also elsewhere on the board
/STM_TX/RK_RX: U4.42 (USART1_TX); also elsewhere on the board
GND: C53.1, C54.1, C55.1, C56.1, C57.1, C58.1, C59.1, C60.1, C61.2, U4.12 (VSSA), U4.18 (VSS), U4.31 (VSS), U4.47 (VSS), U4.63 (VSS); also elsewhere on the board
unnamed: R32.2, U4.60 (PH3)
unnamed: C61.1, U4.30 (VCAP)

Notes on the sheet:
IMU
USR
PMIC
VDDA/VBAT unused
Internal osc. sufficient
FC CTRL
RK3566 CTRL/DATA
SWD
